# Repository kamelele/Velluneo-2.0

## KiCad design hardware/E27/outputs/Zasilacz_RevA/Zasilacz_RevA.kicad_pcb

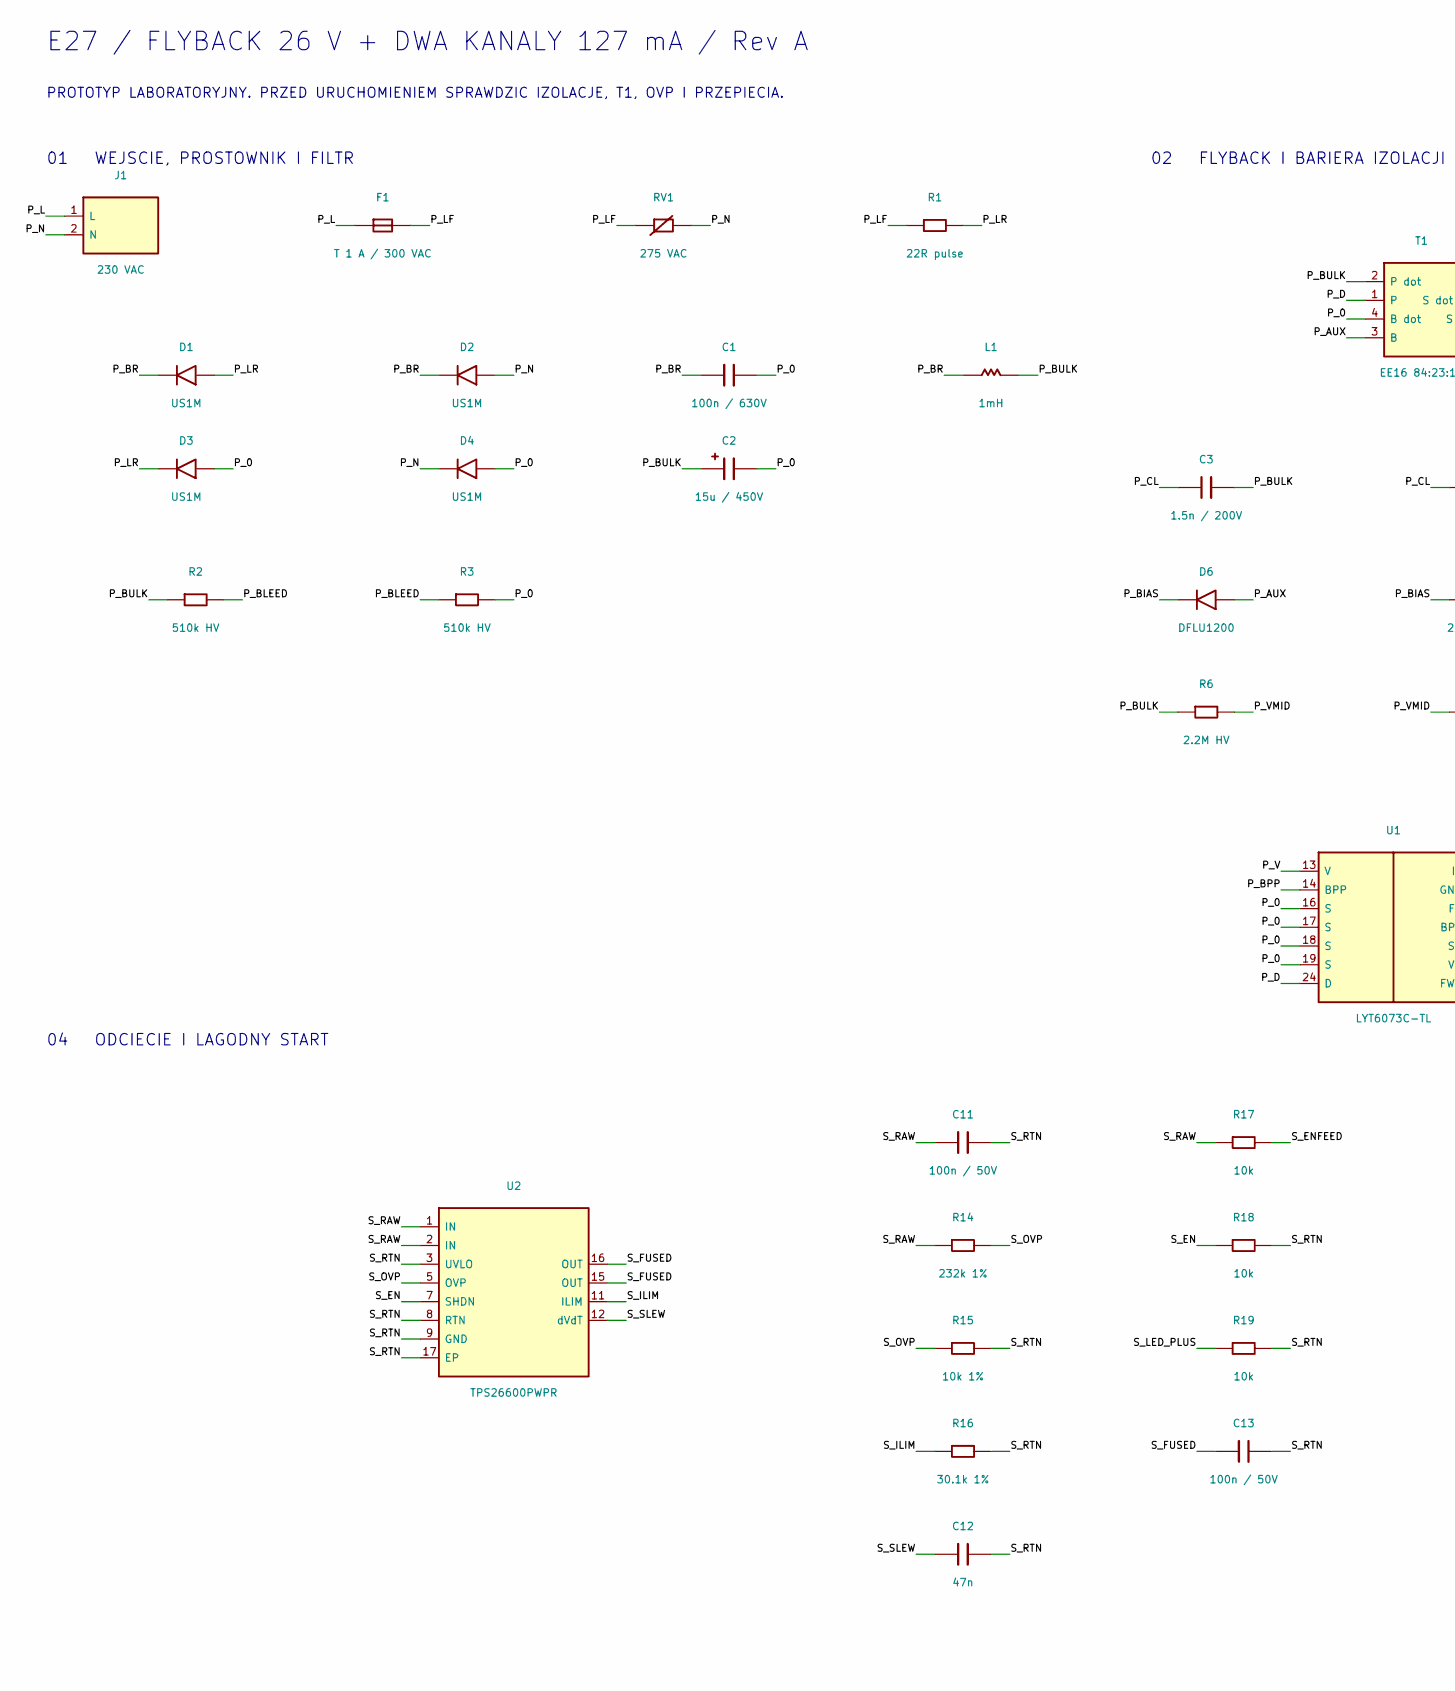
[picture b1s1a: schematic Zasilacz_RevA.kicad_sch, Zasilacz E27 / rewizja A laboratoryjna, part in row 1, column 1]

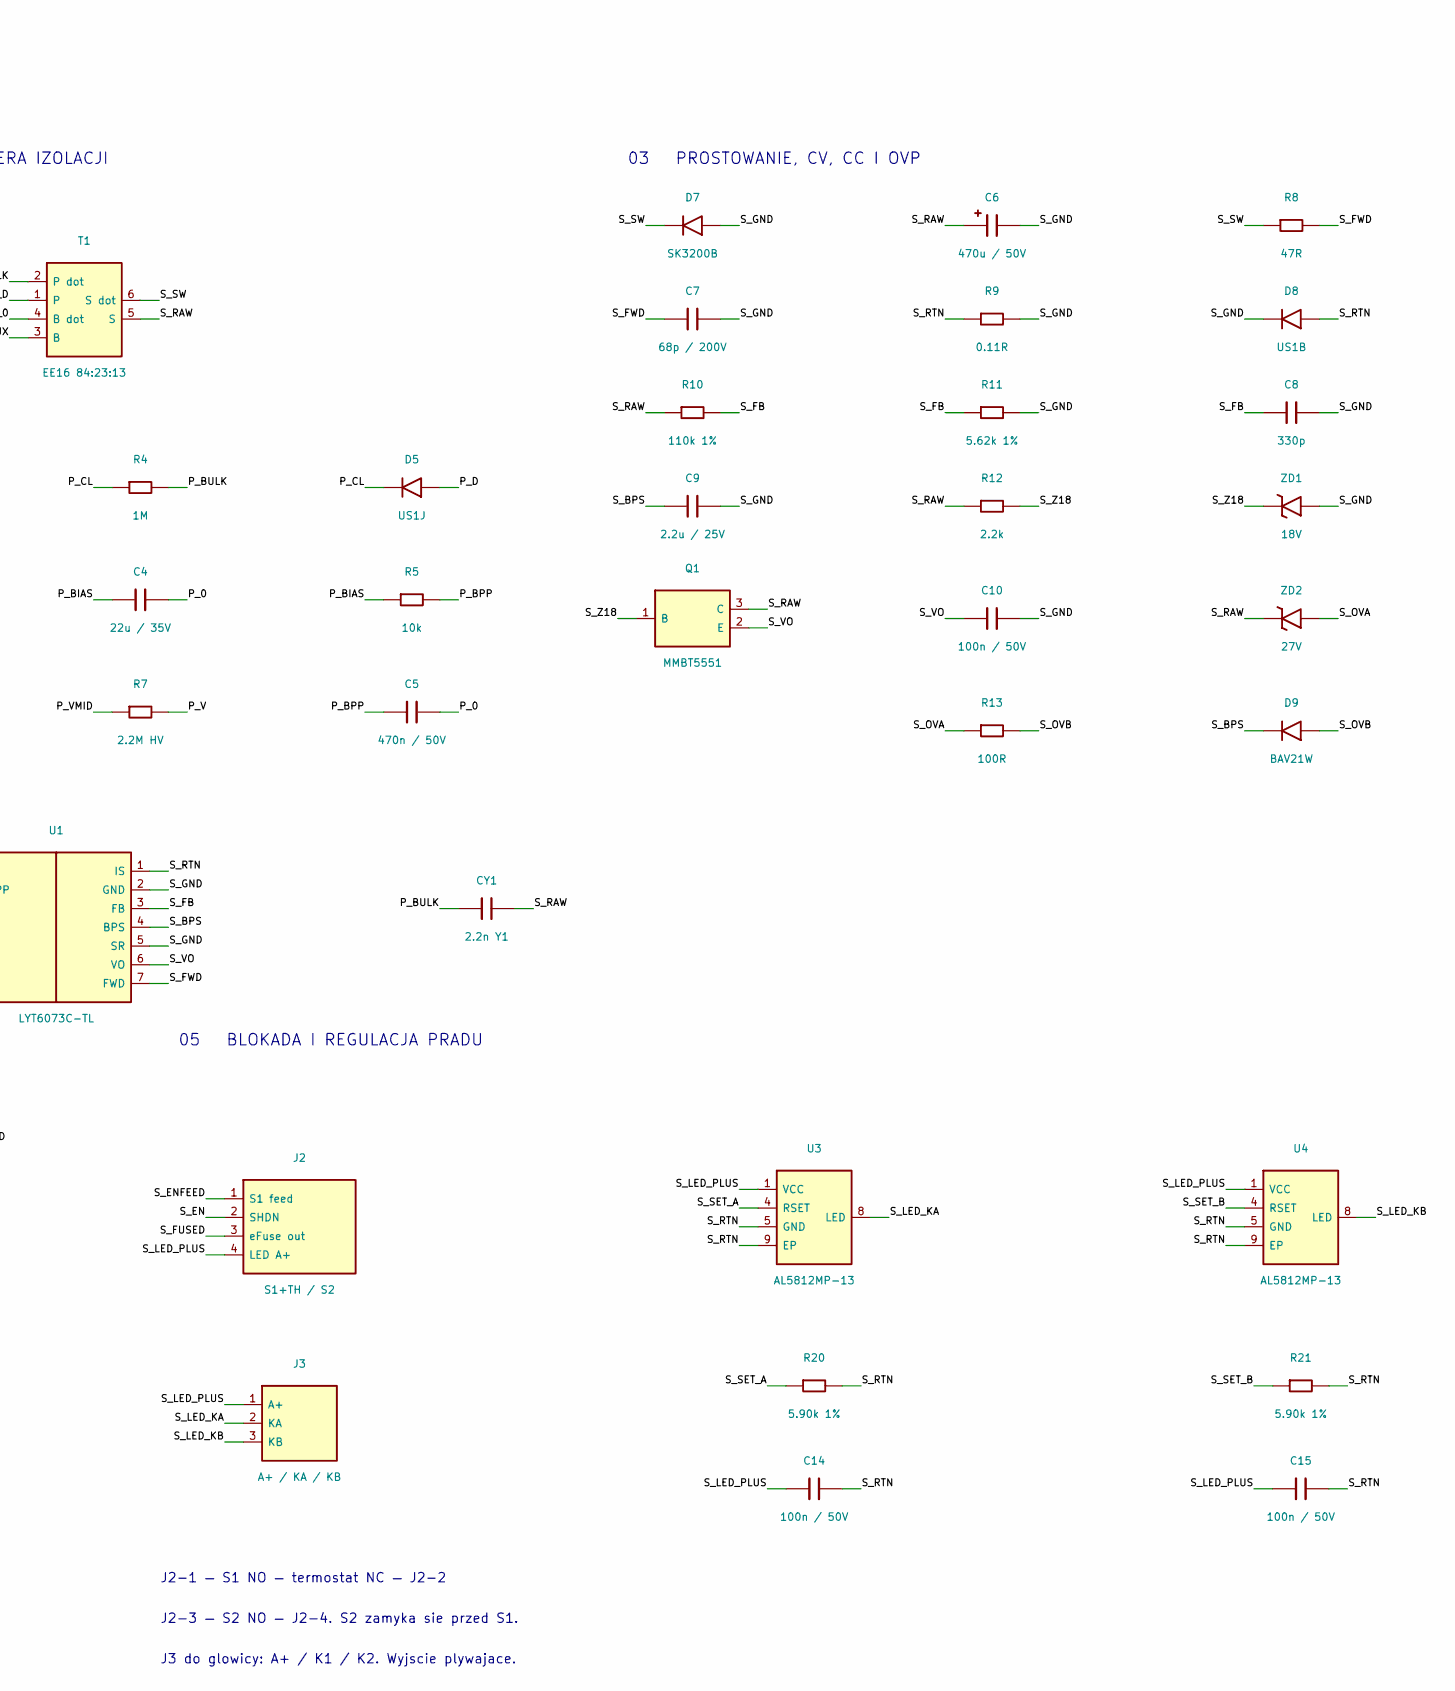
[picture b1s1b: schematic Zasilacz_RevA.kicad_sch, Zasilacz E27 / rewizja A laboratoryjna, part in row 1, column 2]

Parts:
C1: 100n / 630V; C_1210_3225Metric
C2: 15u / 450V; CP_Radial_D10.0mm_P5.00mm
C3: 1.5n / 200V; C_0805_2012Metric
C4: 22u / 35V; C_1206_3216Metric
C5: 470n / 50V; C_0805_2012Metric
C6: 470u / 50V; CP_Radial_D12.5mm_P5.00mm
C7: 68p / 200V; C_0603_1608Metric
C8: 330p; C_0603_1608Metric
C9: 2.2u / 25V; C_1206_3216Metric
C10, C11, C13, C14, C15: 100n / 50V; C_0805_2012Metric
C12: 47n; C_0603_1608Metric
CY1: 2.2n Y1; CY1_10mm
D1, D2, D3, D4: US1M; D_SMA
D5: US1J; D_SMA
D6: DFLU1200; D_PowerDI-123
D7: SK3200B; D_SMB
D8: US1B; D_SMA
D9: BAV21W; D_SOD-123
F1: T 1 A / 300 VAC; Fuse_TE5
J1: 230 VAC; Mains_L_N
J2: S1+TH / S2; JST_XH_B4B-XH-A_1x04_P2.50mm_Vertical
J3: A+ / KA / KB; JST_XH_B3B-XH-A_1x03_P2.50mm_Vertical
L1: 1mH; L_Bourns-SRR1005
Q1: MMBT5551; SOT-23
R1: 22R pulse; R_Axial_DIN0207_L6.3mm_D2.5mm_P10.16mm_Horizontal
R2, R3: 510k HV; R_2010_5025Metric
R4: 1M; R_1206_3216Metric
R5, R19: 10k; R_0805_2012Metric
R6, R7: 2.2M HV; R_2010_5025Metric
R8: 47R; R_0805_2012Metric
R9: 0.11R; R_0805_2012Metric
R10: 110k 1%; R_0603_1608Metric
R11: 5.62k 1%; R_0603_1608Metric
R12: 2.2k; R_0805_2012Metric
R13: 100R; R_0805_2012Metric
R14: 232k 1%; R_0603_1608Metric
R15: 10k 1%; R_0603_1608Metric
R16: 30.1k 1%; R_0603_1608Metric
R17, R18: 10k; R_0603_1608Metric
R20, R21: 5.90k 1%; R_0603_1608Metric
RV1: 275 VAC; TMOV14
T1: EE16 84:23:13; EE16_6pins_RFQ
U1: LYT6073C-TL; InSOP_24D
U2: TPS26600PWPR; PWP0016A
U3, U4: AL5812MP-13; E27_Al5812_MSOP
ZD1: 18V; D_SOD-123
ZD2: 27V; D_SOD-123

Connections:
/P_0: C1.2, C2.2, C4.2, C5.2, D3.2 (A), D4.2 (A), R3.2, T1.4 (B dot), U1.16 (S), U1.17 (S), U1.18 (S), U1.19 (S)
/P_AUX: D6.2 (A), T1.3 (B)
/P_BIAS: C4.1, D6.1 (K), R5.1
/P_BLEED: R2.2, R3.1
/P_BPP: C5.1, R5.2, U1.14 (BPP)
/P_BR: C1.1, D1.1 (K), D2.1 (K), L1.1
/P_BULK: C2.1, C3.2, CY1.1, L1.2, R2.1, R4.2, R6.1, T1.2 (P dot)
/P_CL: C3.1, D5.1 (K), R4.1
/P_D: D5.2 (A), T1.1, U1.24 (D)
/P_L: F1.1, J1.1 (L)
/P_LF: F1.2, R1.1, RV1.1
/P_LR: D1.2 (A), D3.1 (K), R1.2
/P_N: D2.2 (A), D4.1 (K), J1.2 (N), RV1.2
/P_V: R7.2, U1.13 (V)
/P_VMID: R6.2, R7.1
/S_BPS: C9.1, D9.1 (K), U1.4 (BPS)
/S_EN: J2.2 (SHDN), R18.1, U2.7 (SHDN)
/S_ENFEED: J2.1 (S1 feed), R17.2
/S_FB: C8.1, R10.2, R11.1, U1.3 (FB)
/S_FUSED: C13.1, J2.3 (eFuse out), U2.15 (OUT), U2.16 (OUT)
/S_FWD: C7.1, R8.2, U1.7 (FWD)
/S_GND: C6.2, C7.2, C8.2, C9.2, C10.2, D7.2 (A), D8.1 (K), R9.2, R11.2, U1.2 (GND), U1.5 (SR), ZD1.2 (A)
/S_ILIM: R16.1, U2.11 (ILIM)
/S_LED_KA: J3.2 (KA), U3.8 (LED)
/S_LED_KB: J3.3 (KB), U4.8 (LED)
/S_LED_PLUS: C14.1, C15.1, J2.4 (LED A+), J3.1 (A+), R19.1, U3.1 (VCC), U4.1 (VCC)
/S_OVA: R13.1, ZD2.2 (A)
/S_OVB: D9.2 (A), R13.2
/S_OVP: R14.2, R15.1, U2.5 (OVP)
/S_RAW: C6.1, C11.1, CY1.2, Q1.3 (C), R10.1, R12.1, R14.1, R17.1, T1.5 (S), U2.1 (IN), U2.2 (IN), ZD2.1 (K)
/S_RTN: C11.2, C12.2, C13.2, C14.2, C15.2, D8.2 (A), R9.1, R15.2, R16.2, R18.2, R19.2, R20.2, R21.2, U1.1 (IS), U2.3 (UVLO), U2.8 (RTN), U2.9 (GND), U2.17 (EP), U3.5 (GND), U3.9 (EP), U4.5 (GND), U4.9 (EP)
/S_SET_A: R20.1, U3.4 (RSET)
/S_SET_B: R21.1, U4.4 (RSET)
/S_SLEW: C12.1, U2.12 (dVdT)
/S_SW: D7.1 (K), R8.1, T1.6 (S dot)
/S_VO: C10.1, Q1.2 (E), U1.6 (VO)
/S_Z18: Q1.1 (B), R12.2, ZD1.1 (K)

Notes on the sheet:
E27 / FLYBACK 26 V + DWA KANALY 127 mA / Rev A
PROTOTYP LABORATORYJNY. PRZED URUCHOMIENIEM SPRAWDZIC IZOLACJE, T1, OVP I PRZEPIECIA.
01 WEJSCIE, PROSTOWNIK I FILTR
02 FLYBACK I BARIERA IZOLACJI
03 PROSTOWANIE, CV, CC I OVP
04 ODCIECIE I LAGODNY START
05 BLOKADA I REGULACJA PRADU
J2-1 — S1 NO — termostat NC — J2-2
J2-3 — S2 NO — J2-4. S2 zamyka sie przed S1.
J3 do glowicy: A+ / K1 / K2. Wyjscie plywajace.

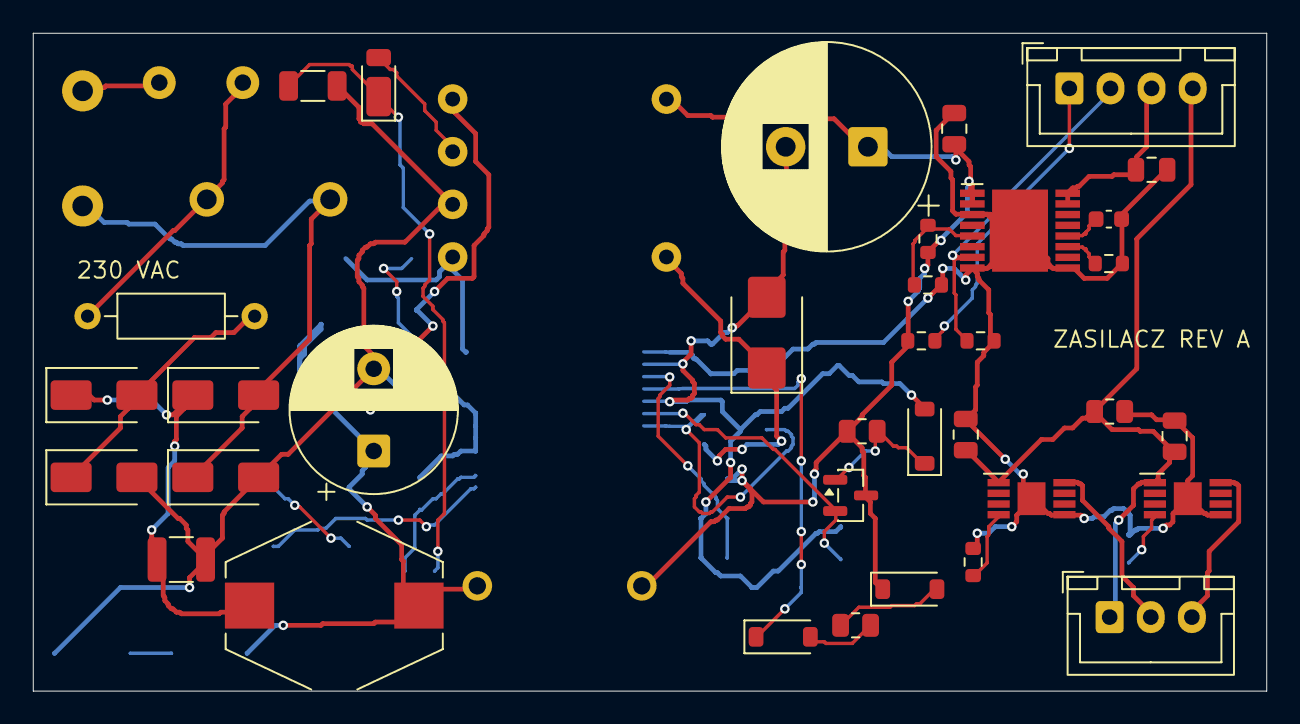
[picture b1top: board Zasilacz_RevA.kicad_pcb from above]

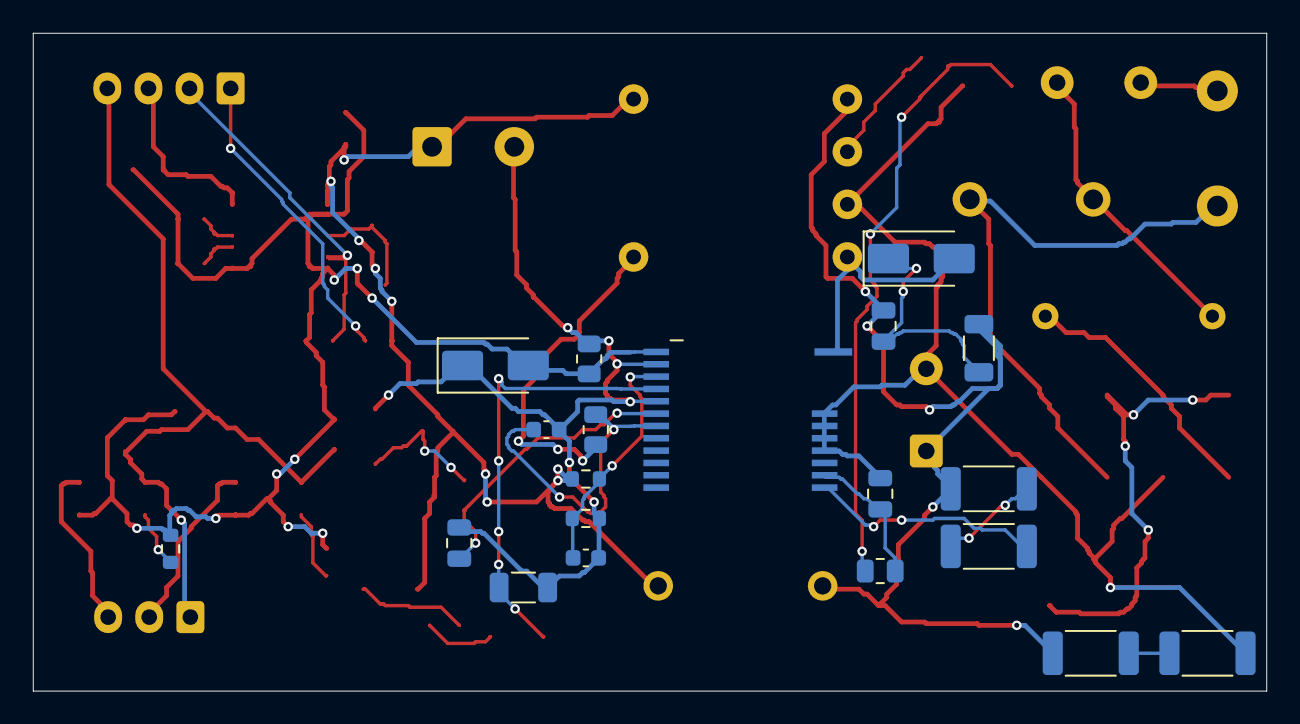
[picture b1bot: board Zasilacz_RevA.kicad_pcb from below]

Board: 2 copper layers, 75.0 x 40.0 mm, 60 parts (20 on the bottom side), 37 nets.

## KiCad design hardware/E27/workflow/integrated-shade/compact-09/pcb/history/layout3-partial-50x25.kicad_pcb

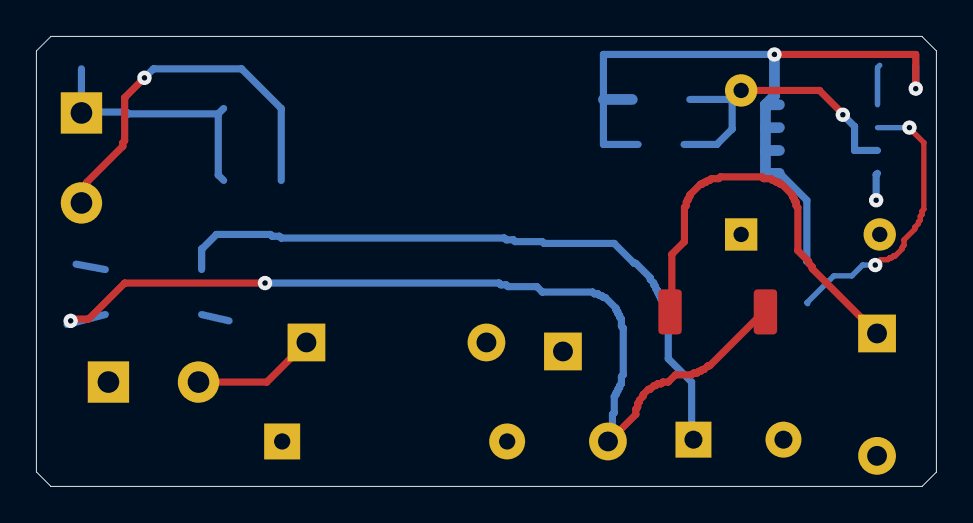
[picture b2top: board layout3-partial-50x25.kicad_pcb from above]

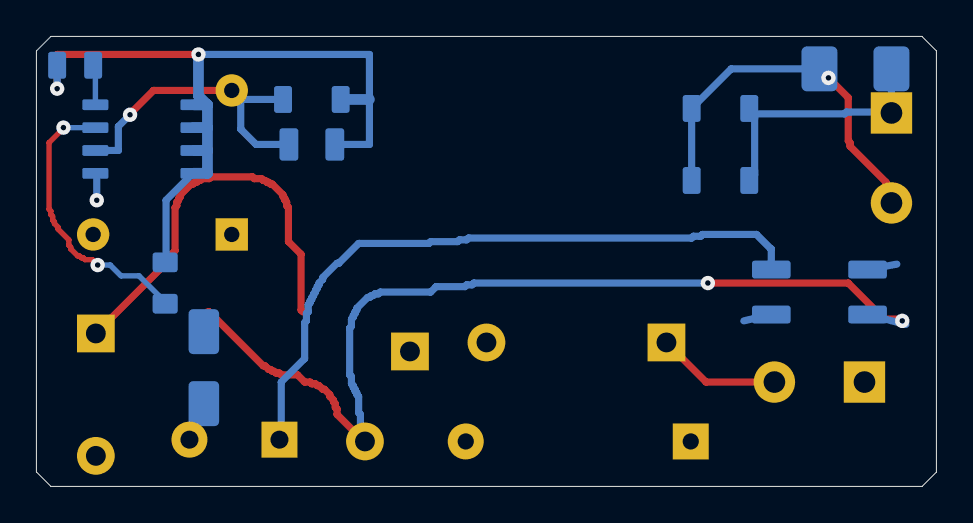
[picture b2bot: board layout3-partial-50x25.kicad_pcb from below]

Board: 2 copper layers, 50.0 x 25.0 mm, 19 parts (10 on the bottom side), 11 nets.

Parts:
BR1: MB10S-13; SC09_BR1
C1: B32529E6473K189; SC09_C1
C4: B32671P6154K000; SC09_C4
C5: CL21B475KAFNNNE; SC09_C5
C6: EEUFS2A151; SC09_C6
D1: US1J-13-F; SC09_D1
J1: Direct insulated-wire solder pads; SC09_J1
J2: Direct insulated-wire solder pads; SC09_J2
L1: RL-5480-3-3300; SC09_L1
R4: ERJ-6ENF1242V; SC09_R4
R5: RL1206FR-7W0R68L; SC09_R5
R6: CRCW12063R65FKEA; SC09_R6
R7: VR25000003903FR500; SC09_R7
R8: RC1206FR-0768KL; SC09_R8
R9: RC1206FR-0768KL; SC09_R9
RF1: FW20A10R0JA; SC09_RF1
RV1: V275LA4P; SC09_RV1
T1: RDR464 EE10 150turn build; SC09_T1
U1: LYT1603D-TL; SC09_U1

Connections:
/AC_FUSED: BR1.2, RF1.2, RV1.1
/AC_L: J1.1, RF1.1
/AC_N: BR1.4, J1.2, RV1.2
/BP: C5.1, U1.1
/BUS_FILTERED: C4.1, L1.2, U1.4
/BUS_RECT: BR1.1, C1.1, L1.1
/DC_RETURN: BR1.3, C1.2, C4.2, C6.2, D1.2, J2.2, R8.2, R9.2
/FB_INDUCTOR: D1.1, R5.2, R6.2, T1.8, U1.3
/LED_PLUS: C6.1, J2.1, R7.2, R8.1, R9.1, T1.1
/M: R4.1, R7.1, U1.2
/SW_SOURCE: C5.2, R4.2, R5.1, R6.1, U1.5, U1.6, U1.7, U1.8

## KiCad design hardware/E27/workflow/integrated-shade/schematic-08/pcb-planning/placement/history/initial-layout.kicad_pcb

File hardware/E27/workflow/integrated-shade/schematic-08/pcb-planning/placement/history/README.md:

HistoricalinitialPCB/source/reportpacketwasrejectedbeforehumanplacementreviewbecauseofRC-PLACEMENT-01. It isnotanactiveCADsource. ActivePCBisonlyhardware/E27/variants/integrated-shade/SC08_prototype/SC08_prototype.kicad_pcb. Exactinitialpacketincludingoldexternalimageswasarchivedlocallywork/sc08-placement-initial-rejected.zip. Current review-inputs.json andfinalrole reports govern correctedcandidate.

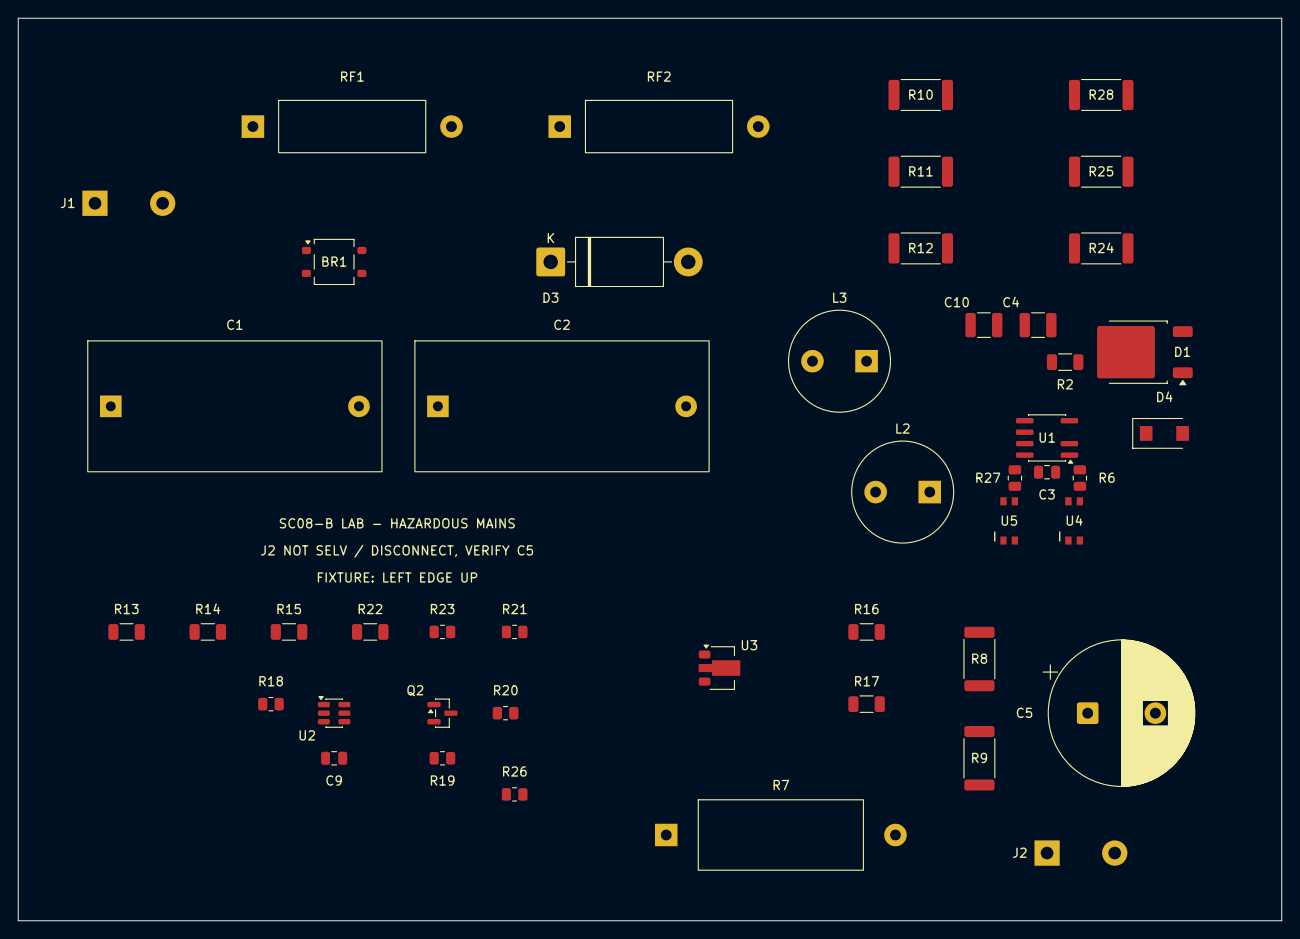
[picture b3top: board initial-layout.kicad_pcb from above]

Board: 2 copper layers, 140.0 x 100.0 mm, 47 parts (0 on the bottom side), 30 nets, no tracks yet.

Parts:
BR1: 1000V0.8A; MB10S_Diodes
C1: 100nF2kV; Film_32x14_P27p5
C2: 330nF1kV; Film_32x14_P27p5
C3, C9: 100nF50V; C_0805
C4, C10: 22uF25VX7R; C_1210_3225Metric
C5: 150uF160V; CP_16x25_P7p5
D1: 1200V2ASiC; C4D02120E_TO252
D3: 376Vstandoff TVS; D_DO-201AD_P15.24mm_Horizontal
D4: 1000V1A blocking; D_SMA
J1: AC input230V50Hz; WirePads_2_P7p5
J2: LED panel55mA; WirePads_2_P7p5
L2, L3: 1.5mH; RFC1010B_P6
Q2: P-MOS20V; SOT23
R2: 28.7ohm 0.75W HP current seed; R_1206
R6: 100RBPclamp; R_0805
R7: 470R5W; AC05_18x7p5_P25p4
R8, R9: 56k1W; R_2512
R10, R11, R12, R24, R25, R28: 715ohm1.5WHP; R_2512
R13, R14: 160k0.1%10ppm; R_1206
R15: 1k0.1%10ppm; R_1206
R16: 38k3 0.1%; R_1206
R17: 10k 0.1%; R_1206
R18: 100R; R_0805
R19: 11k; R_0805
R20: 10k; R_0805
R21, R26: 1k78 0.5W HP; R_0805
R22: 210k0.1%10ppm; R_1206
R23: 4k3; R_0805
R27: 100ohmBPclamp2; R_0805
RF1, RF2: 220R2Wfusible; RF_16x5p5_P22
U1: LYT0006D-TL; LYT_SO8C_no3
U2: TLV6700DDCR; SOT23_6
U3: TL431BQPK SOT89; SOT-89-3
U4, U5: AQY221R2VY; Panasonic_SSOP4

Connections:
/AUX_FEED5: R25.2, R28.1
/BP: C3.1, R6.1, R27.1, U1.1
/COUT_PLUS: C5.1, L3.2, R7.1, R8.1, R9.1, R10.1, R13.1
/DC_RETURN: BR1.3, C1.2, C2.2, C5.2, C9.2, D1.2, D3.2, J2.2, R8.2, R9.2, R15.2, R17.2, R23.2, U2.2, U2.3, U3.2, U4.2, U5.2
/DRAIN_BLOCKED: D4.1, U1.4
/LED_PLUS: J2.1, R7.2
/MOS_GATE: Q2.1, R19.1, R20.2
/OPTO_DRIVE: Q2.3, R21.1, R22.1, R23.1, R26.1
/OV_LOW: R19.2, U2.6
/OV_SENSE: R14.2, R15.1, R22.2, U2.4
/RAIL_REF: R16.2, R17.1, U3.1
/SENSE_FB: C4.1, C10.1, D1.1, D1.CASE, R2.2, U1.2
/SOURCE: C3.2, C4.2, C10.2, L2.1, R2.1, U1.5, U1.6, U1.7, U1.8, U4.4, U5.4
/VCC_OV: Q2.2, R16.1, R18.1, R20.1, R28.2, U3.3
/VDD_COMP: C9.1, R18.2, U2.5
unnamed: BR1.1, C1.1, C2.1, D3.1, D4.2
unnamed: BR1.2, RF2.2
unnamed: J1.1, RF1.1
unnamed: BR1.4, J1.2
unnamed: L2.2, L3.1
unnamed: R6.2, U4.3
unnamed: R10.2, R11.1
unnamed: R11.2, R12.1
unnamed: R12.2, R24.1
unnamed: R13.2, R14.1
unnamed: R24.2, R25.1
unnamed: R27.2, U5.3
unnamed: RF1.2, RF2.1
unnamed: R21.2, U4.1
unnamed: R26.2, U5.1

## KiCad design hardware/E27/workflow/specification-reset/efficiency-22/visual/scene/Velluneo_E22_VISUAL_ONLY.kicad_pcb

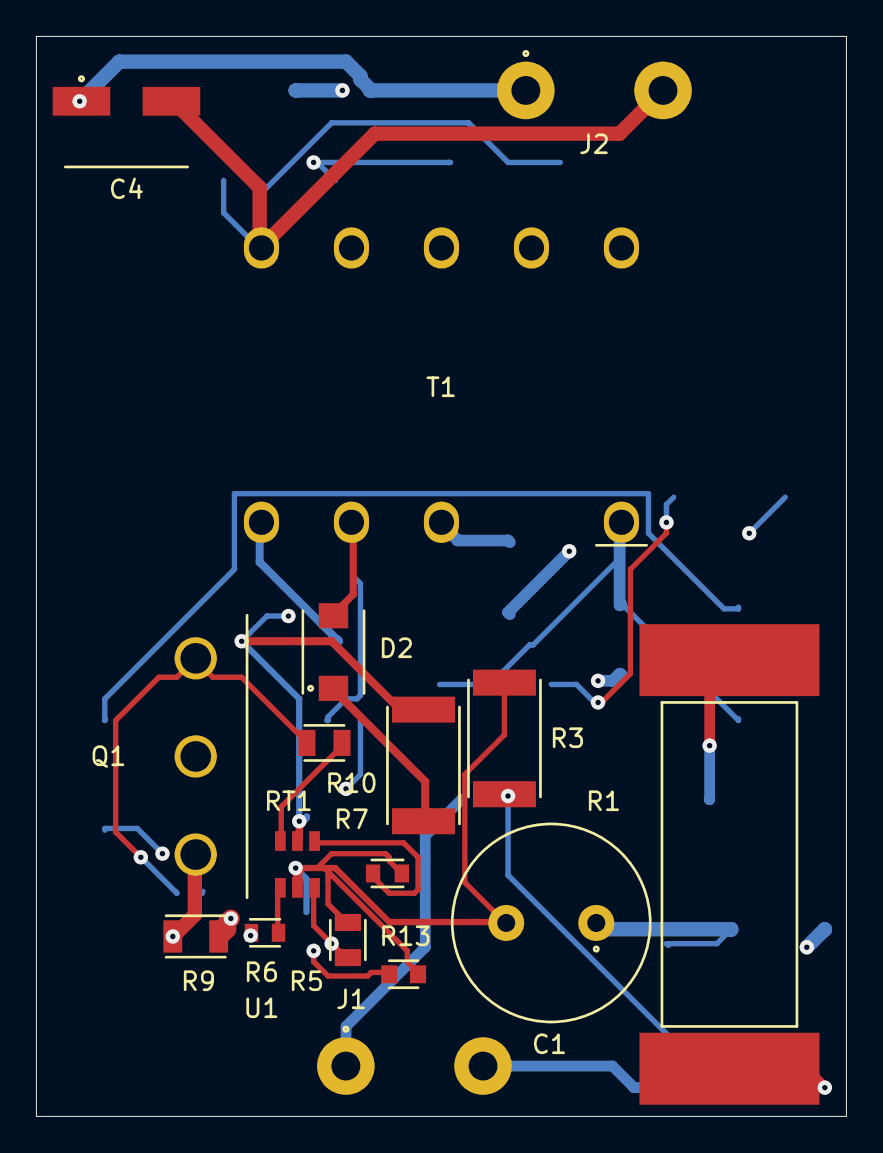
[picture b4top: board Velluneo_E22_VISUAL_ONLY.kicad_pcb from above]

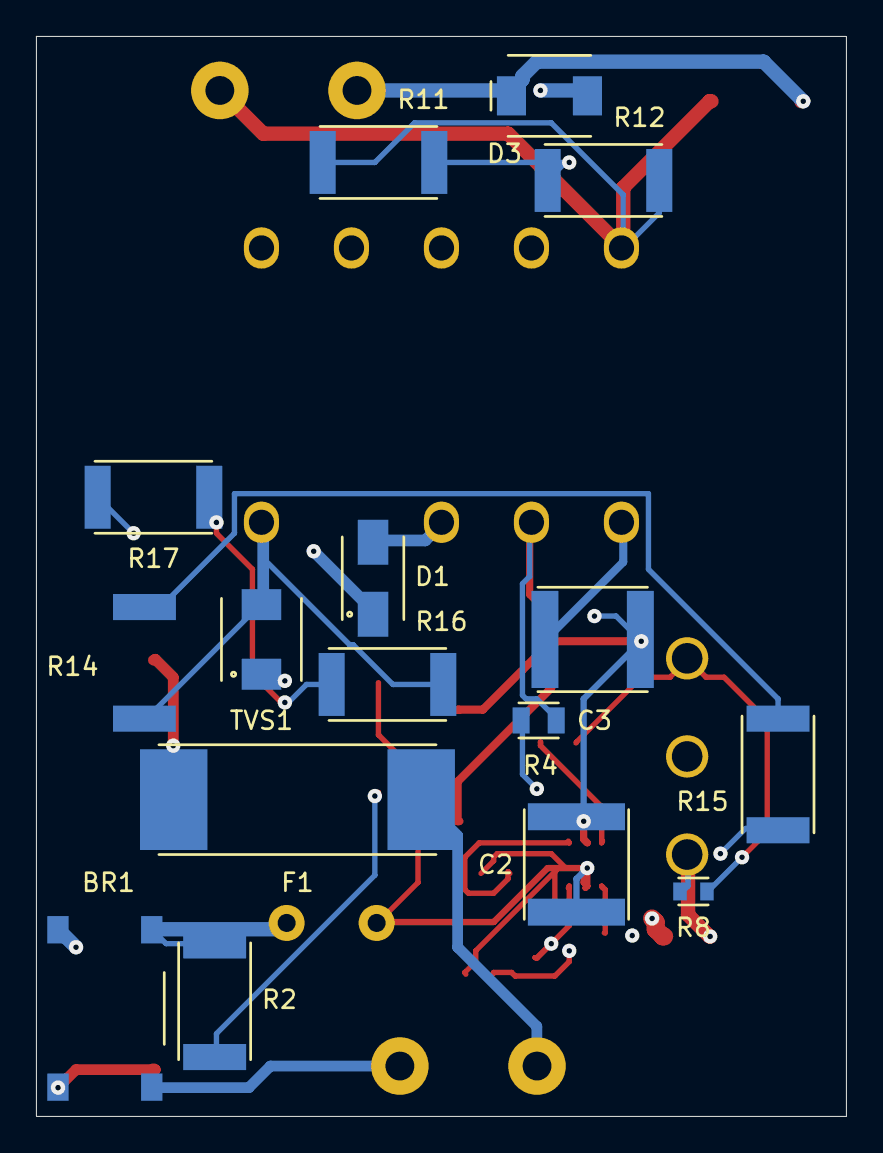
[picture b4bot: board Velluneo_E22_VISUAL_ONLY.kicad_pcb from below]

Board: 4 copper layers, 45.0 x 60.0 mm, 33 parts (16 on the bottom side), 23 nets.

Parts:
BR1: SDB107-TP / 1000V; MCC_SDB107_SDB1_FACTORY
C1: 15u / 450V; Rubycon_BXW_D10_P5_PROJECT_CANDIDATE
C2, C3: 470n / 50V C0G; KEMET_2220_C0G_DensityB_Native
C4: 10u / 63V HYBRID; Panasonic_ZA_D_Standard_Native
D1: US1M-13-F; Diodes_US1M_SMA_Native
D2: STTH1R02A; ST_STTH_SMA_Native
D3: STPS2200U; STPS2200U_SMB_ST
F1: 250mA / 277VAC; SCHURTER_UMTH_WEB_PROVISIONAL
J1: E27 INTERNAL WIRES; InternalWirePair_P7p62_D1p6_PROJECT_CANDIDATE
J2: INTERNAL LED WIRES; InternalWirePair_P7p62_D1p6_PROJECT_CANDIDATE
Q1: STFW2N105K5 / 1050V; STFW2N105K5_TO3PF_STRAIGHT
R1: 47R / AC05-AT WSZ; Vishay_AC05AT_WSZ_FACTORY
R2, R3, R15: 499k; CRCW_2512_NativeReflow
R4: 53.6k; CRCW_0805_NativeReflow
R5: 20.0k; CRCW_0805_NativeReflow
R6: 2.00k; CRCW_0603_NativeReflow
R7: 4.7R; CRCW_0805_NativeReflow
R8: 47k; CRCW_0603_NativeReflow
R9: 1.80R; CRCW_1206_NativeReflow
R10: 4.7R; CRCW_2512_NativeReflow
R11, R12: 20k; CRCW_2512_NativeReflow
R13: 84.5k / 0.1% 25ppm; TNPW0603_IPC_Reflow
R14: 499k; CRCW_2512_R14_SilkClear
R16, R17: 422k / startup; CRCW_2512_NativeReflow
RT1: 100k / B4100; NTCS0603_NativeReflow
T1: 72:18:10 / 1.1mH; MYRRA74032_E25_FACTORY
TVS1: Littelfuse SMBJ160A; Vishay_SMBJ_PROJECT_CANDIDATE
U1: UCC28701DBVT; UCC28701_DBV_Native

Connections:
/AUX_RAW: D2.2, R4.1, T1.2
/BLEED_MID_B: R14.2, R15.1
/BULK_POS: BR1.1, C1.1, R2.1, R14.1, R16.1, T1.5, TVS1.2
/CS: R6.2, U1.4
/DRAIN: D1.2, Q1.2, T1.3
/DRV: R7.1, U1.3
/GATE: Q1.1, R7.2, R8.1
/NTC: RT1.1, U1.1
/OUTPUT_NEG: C4.2, J2.2, R11.2, R12.2, T1.10
/OUTPUT_POS: C4.1, D3.1, J2.1, R11.1, R12.1
/PRIMARY_GND: BR1.3, C1.2, C2.2, C3.2, R3.2, R5.2, R9.2, R13.2, R15.2, RT1.2, T1.1, U1.5
/SECONDARY_RAW: D3.2, T1.6
/SENSE: Q1.3, R6.1, R8.2, R9.1
/STARTUP_MID: R16.2, R17.1
/VDD: C2.1, C3.1, R10.2, R13.1, R17.2, U1.2
/VS: R4.2, R5.1, U1.6
unnamed: BR1.2, J1.2
unnamed: BR1.4, R1.2
unnamed: D1.1, TVS1.1
unnamed: D2.1, R10.1
unnamed: F1.1, J1.1
unnamed: F1.2, R1.1
unnamed: R2.2, R3.1
